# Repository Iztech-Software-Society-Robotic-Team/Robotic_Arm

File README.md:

# Robotic Arm

This project is made for IZTECH Software Society by IZTECH Software Society's robotic team.

Server -> Talha Karakaya, Deniz Ege Özcan

WebUI -> Hakan Bağıç(KebanFiru)

ESP32 Branch:
- Hardware design of mainboard -> Hakan Bağıç(KebanFiru)
- Embedded code of ESP32 -> Hakan Bağıç(KebanFiru)

RasberryPi Branch:
- Hardware design of mainboard -> Murat Işık
- Design of speaker and microphone -> Murat Işık
- Refactor server code for work on RasberryPi -> Murat Işık
 
For more information you can check our documantation.

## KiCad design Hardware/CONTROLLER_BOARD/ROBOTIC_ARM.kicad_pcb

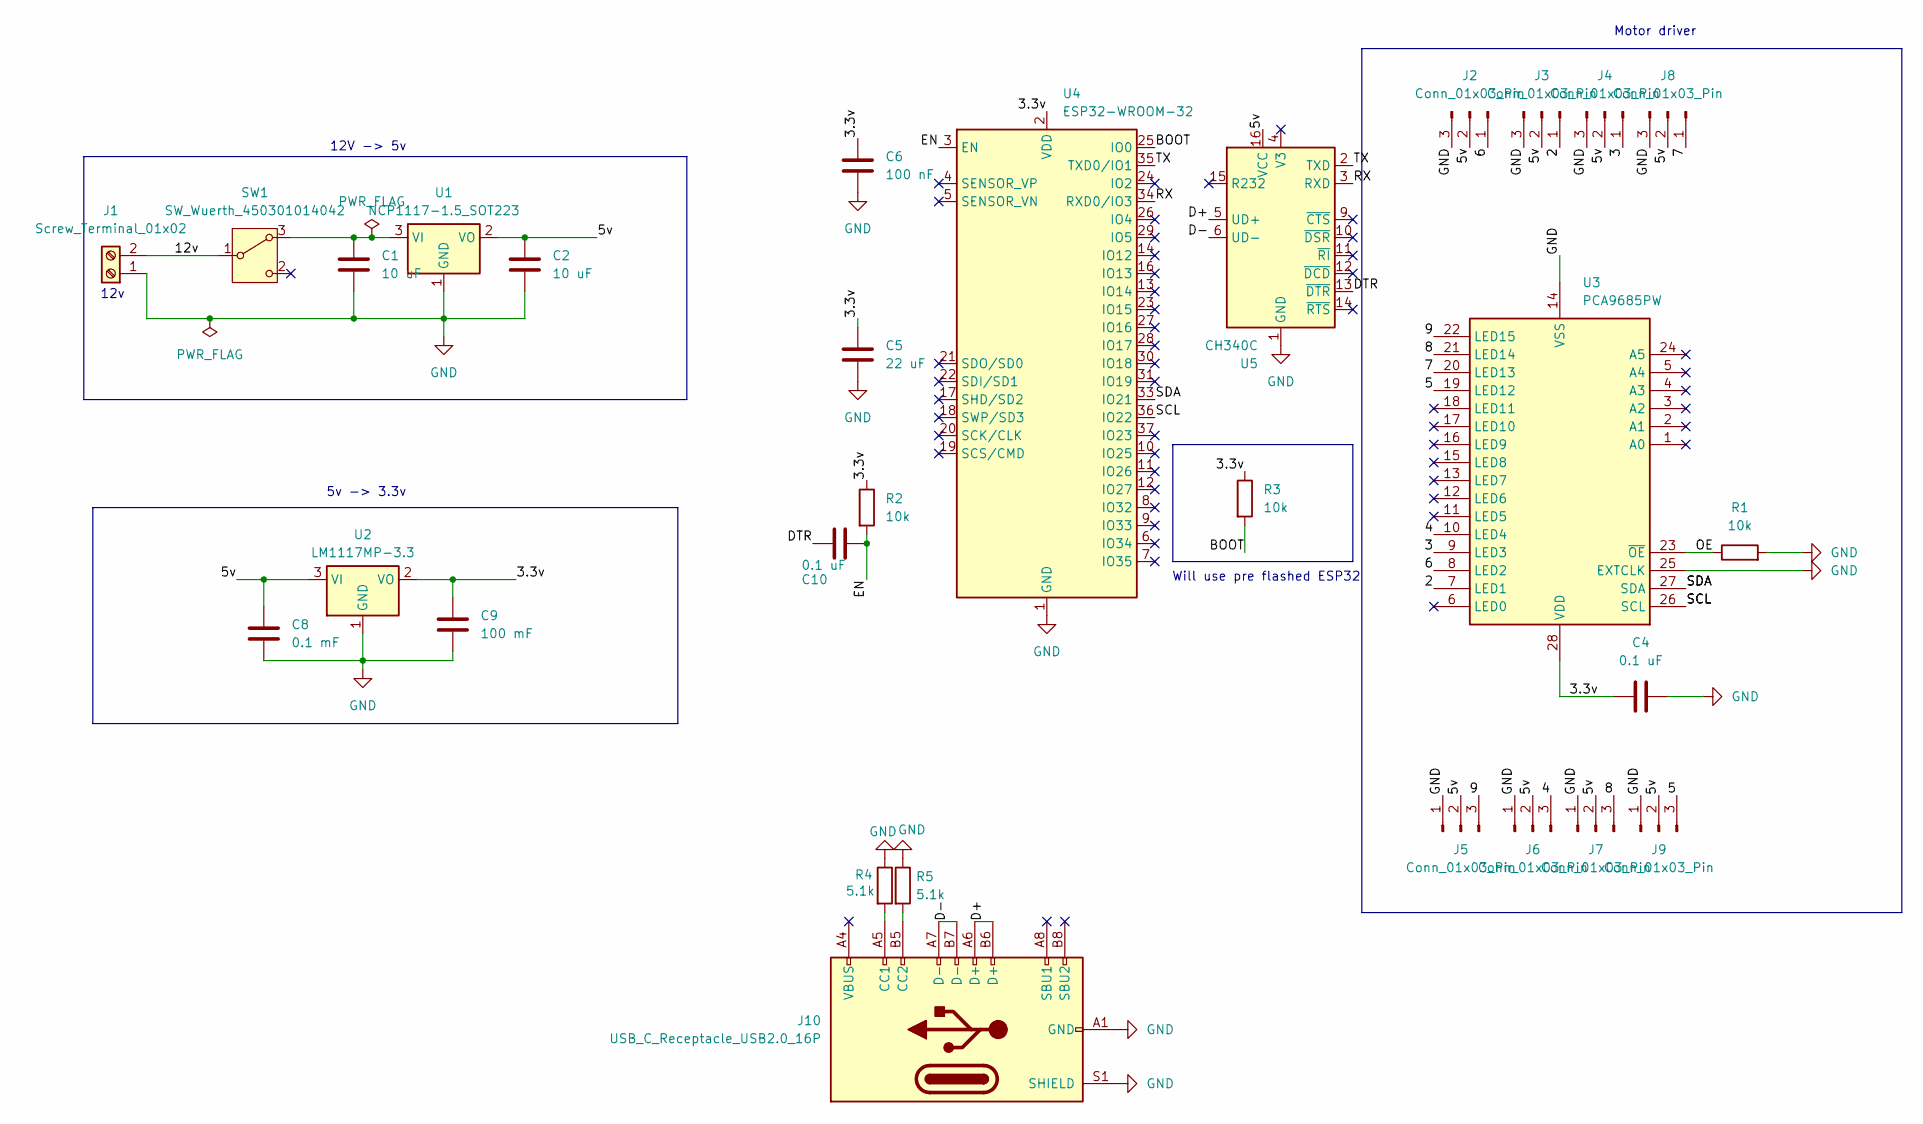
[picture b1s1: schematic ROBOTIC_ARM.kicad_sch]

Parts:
C1, C2: 10 uF; C_0201_0603Metric
C4, C10: 0.1 uF; C_0201_0603Metric
C5: 22 uF; C_0201_0603Metric
C6: 100 nF; C_0201_0603Metric
C8: 0.1 mF; C_0201_0603Metric
C9: 100 mF; C_0201_0603Metric
J1: Screw_Terminal_01x02; TerminalBlock_Altech_AK300-2_P5.00mm
J2, J3, J4, J5, J6, J7, J8, J9: Conn_01x03_Pin; FanPinHeader_1x03_P2.54mm_Vertical
J10: USB_C_Receptacle_USB2.0_16P; USB_C_Receptacle_Amphenol_124019772112A
R1, R2, R3: 10k; R_0201_0603Metric
R4, R5: 5.1k; R_0201_0603Metric
SW1: SW_Wuerth_450301014042; SW_Slide-03_Wuerth-WS-SLTV_10x2.5x6.4_P2.54mm
U1: NCP1117-1.5_SOT223; SOT-223-3_TabPin2
U2: LM1117MP-3.3; SOT-223-3_TabPin2
U3: PCA9685PW; TSSOP-28_4.4x9.7mm_P0.65mm
U4: ESP32-WROOM-32
U5: CH340C; SOIC-16_3.9x9.9mm_P1.27mm

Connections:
/2: J3.1, U3.7 (LED1)
/3: J4.1, U3.9 (LED3)
/3.3v: C4.1, C5.1, C6.1, C9.1, R2.1, R3.1, U2.2 (VO), U3.28 (VDD), U4.2 (VDD)
/4: J6.3, U3.10 (LED4)
/5: J9.3, U3.19 (LED12)
/5v: C2.1, C8.1, J2.2, J3.2, J4.2, J5.2, J6.2, J7.2, J8.2, J9.2, U1.2 (VO), U2.3 (VI), U5.16 (VCC)
/6: J2.1, U3.8 (LED2)
/7: J8.1, U3.20 (LED13)
/8: J7.3, U3.21 (LED14)
/9: J5.3, U3.22 (LED15)
/12v: J1.2, SW1.1 (B)
/BOOT: R3.2, U4.25 (IO0)
/D+: J10.A6 (D+), J10.B6 (D+), U5.5 (UD+)
/D-: J10.A7 (D-), J10.B7 (D-), U5.6 (UD-)
/DTR: C10.1, U5.13 (~DTR)
/EN: C10.2, R2.2, U4.3 (EN)
/OE: R1.1, U3.23 (~OE)
/RX: U4.34 (RXD0/IO3), U5.3 (RXD)
/SCL: U3.26 (SCL), U4.36 (IO22)
/SDA: U3.27 (SDA), U4.33 (IO21)
/TX: U4.35 (TXD0/IO1), U5.2 (TXD)
GND: C1.2, C2.2, C4.2, C5.2, C6.2, C8.2, C9.2, J1.1, J2.3, J3.3, J4.3, J5.1, J6.1, J7.1, J8.3, J9.1, J10.A1 (GND), J10.A12 (GND), J10.B1 (GND), J10.B12 (GND), J10.S1 (SHIELD), R1.2, R4.1, R5.1, U1.1 (GND), U2.1 (GND), U3.14 (VSS), U3.25 (EXTCLK), U4.1 (GND), U4.15 (GND), U4.38 (GND), U4.39 (GND), U5.1 (GND)
unnamed: J10.A5 (CC1), R4.2
unnamed: J10.B5 (CC2), R5.2
unnamed: C1.1, SW1.3 (A), U1.3 (VI)

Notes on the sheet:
12V -> 5v
12v
5v -> 3.3v
Will use pre flashed ESP32
Motor driver

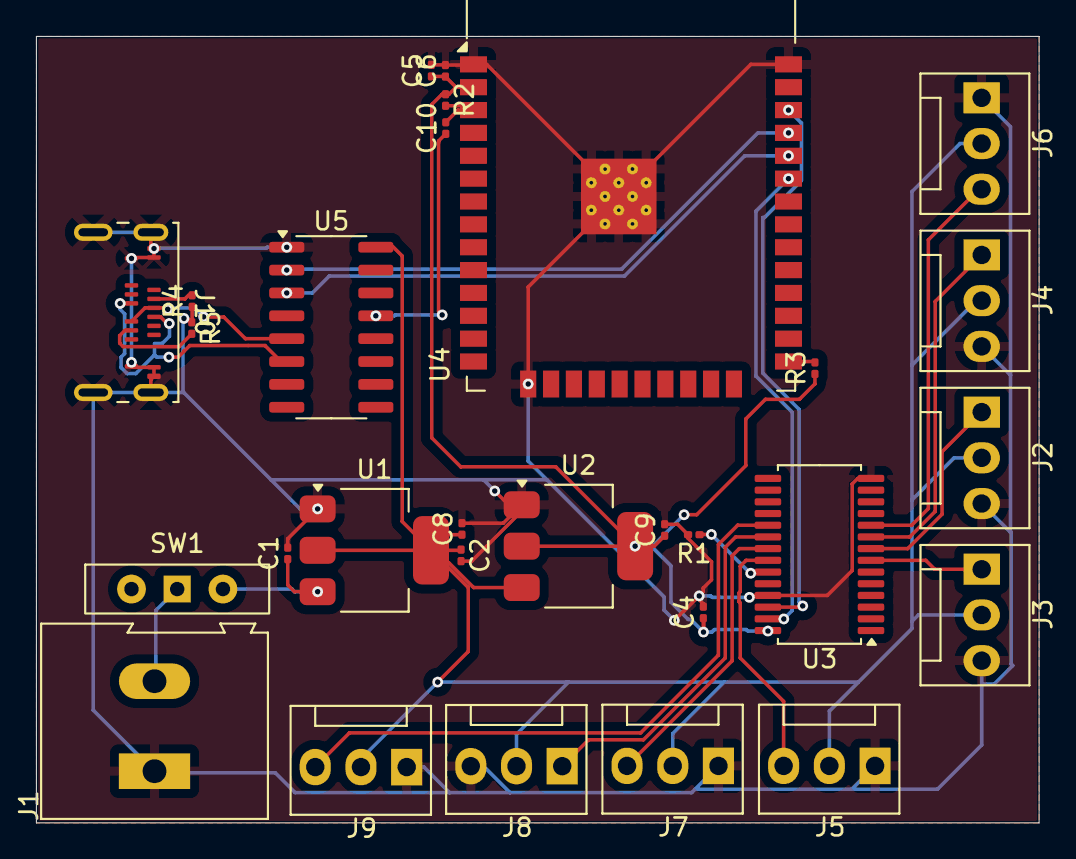
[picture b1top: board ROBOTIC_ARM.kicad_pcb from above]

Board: 2 copper layers, 55.7 x 43.7 mm, 29 parts (0 on the bottom side), 25 nets.

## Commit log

2025-08-06 main code for ESP32 is added
2025-08-10 Update on PCB design
2025-08-10 Rewritten ESP32 structure
2025-08-10 New main.c
2025-08-12 Project structure is changed
